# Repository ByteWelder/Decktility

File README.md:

# Decktility

Decktility is a handheld PC, inspired by [Yarh.io Micro 2](https://yarh.io/),
[uConsole](https://www.clockworkpi.com/uconsole) and various retro handheld PCs.

It is built with a Raspbery Pi CM4 and an 800x480 pixel IPS screen with capacitive touch.
A set of batteries is estimated to provide about 6 hours of power. (\*)

The original build log and learnings can be found on [ByteWelder.com](https://bytewelder.com/posts/2023/05/20/building-a-handheld-pc.html).

# Features & Specifications

- Compact design: `124.4 x 144.0 x 16.3 mm` (w x h x d). The battery lid portrudes by `10.2 mm`.
- Weighs approximately `375 g`. (depends on filament weight)
- Powered by a Raspberry Pi CM4 and a BTT Pad 5 (`800x480` resolution with capacitive touch)
- Replaceable batteries
- USB-C charging (~`10 W`)
- Power management

(\*) Using US18650VTC6 cells. Power draw was tested with an idle Discord tab in Chrome.

# Software

## Raspberry Pi

The Pi can be used with [Raspberry Pi OS](https://www.raspberrypi.com/software/) or any other Pi-compatible OS.

Check the to the [Pad 5 Manual](https://github.com/bigtreetech/Raspberry-Pad/tree/master/Pad5) for installing the OS and setting up some of the hardware.

## Arduino Nano / Power Manager

The [Power Manager](./powermanager) controls the power connection to the Pi and the keyboard. Power is enabled/disabled depending on the battery voltage.
The power manager measures battery and charging status, and can send it to the Pi. This enables battery status on the Pi desktop.
If something is not clear - or if you find an error, please open an issue on the GitHub project page.

Check out the [assembly guide](docs/assembling.md) for more details.

# Case

The latest printable parts are in the [printables](printables) folder.

The case is available as open hardware via OnShape:
- [v1.1](https://cad.onshape.com/documents/bcf3b5212bb2ba6496cfe6cf/v/382999b629ab56cddd2b7e21/e/5dfdd5987e1df112fcfa814b)
- [Main/WIP](https://cad.onshape.com/documents/bcf3b5212bb2ba6496cfe6cf/w/d70be68a60b4c80f684ba746/e/f2fb47dfa2dbdc91d7666ed1)

**Warning**: Don't print from the Main branch, because it will possibly have unfinished and/or untested changes.

# Building

Build this project at [your own risk](LICENSE.md).
The build guide might have flaws.
Working with batteries and electronics is not without risk.

- [Bill of materials](docs/bom.md)
- [Printing guide](docs/printing.md)
- [Assembling](docs/assembling.md)

# License

All hardware, software and other content in this project are licensed under `Attribution-ShareAlike 4.0 International (CC BY-SA 4.0)`.

See [LICENSE.md](LICENSE.md) for details. For a short overview and translations go to the [Creative Commons website](https://creativecommons.org/licenses/by-sa/4.0/legalcode).

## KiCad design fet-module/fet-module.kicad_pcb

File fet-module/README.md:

This is the KiCad project for the FET board, which acts as an electronic switch to turn on/off the hardware depending on available battery power.

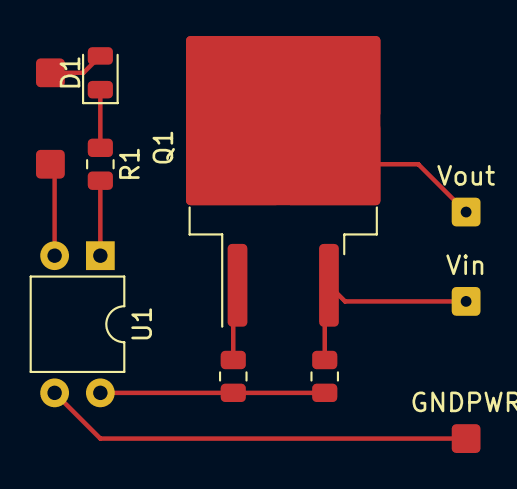
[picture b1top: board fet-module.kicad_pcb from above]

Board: 2 copper layers, 11 parts (0 on the bottom side), 9 nets.

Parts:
+5VD: SolderWire-0.1sqmm_1x01_D0.4mm_OD1mm
D1: LED; LED_0805_2012Metric
GNDD: SolderWire-0.1sqmm_1x01_D0.4mm_OD1mm
GNDPWR: SolderWire-0.1sqmm_1x01_D0.4mm_OD1mm
Q1: PMOS; TO-263-2
R1: 2.2k; R_0805_2012Metric
R2: 10k; R_0805_2012Metric
R3: 1M; R_0805_2012Metric
U1: PC817; DIP-4_W7.62mm
Vin: SolderWire-0.1sqmm_1x01_D0.4mm_OD1mm
Vout: SolderWire-0.1sqmm_1x01_D0.4mm_OD1mm

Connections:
+5VD: +5VD.1, D1.2 (A)
GNDD: GNDD.1, U1.2
GNDPWR: GNDPWR.1, U1.3
unnamed: D1.1 (K), R1.1
unnamed: Q1.1 (D), R2.2
unnamed: R1.2, U1.1
unnamed: R2.1, R3.2, U1.4
VD: Q1.2 (G), Vout.1
VDD: Q1.3 (S), R3.1, Vin.1

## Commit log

2023-05-02 added empty README.md
2023-05-02 added powermanager and powermanager-client
2023-05-02 fix link
2023-05-02 added link
2023-05-02 added OnShape
2023-05-03 added mockup image
2023-05-03 updated image
2023-05-03 added license
2023-05-03 added features
2023-05-03 added dimensions
2023-05-03 rephrased
2023-05-03 typo
2023-05-03 image update
2023-05-04 design update
2023-05-04 new graphic
2023-05-04 updated BOM
2023-05-04 fix left edge
2023-05-04 size limit test
2023-05-04 revert
2023-05-08 updated docs
2023-05-08 updated pics
2023-05-12 printing tips
2023-05-13 beta update
2023-05-13 center image
2023-05-13 updated project description
2023-05-13 added photo
2023-05-13 weight update
2023-05-13 battery life
2023-05-14 docs improved
2023-05-14 updated info about parts
2023-05-14 fixed bom pics links
2023-05-14 building notes
2023-05-14 move pics to docs folder
2023-05-14 added power manager info
2023-05-14 updated todo list
2023-05-14 updated todo list after fixes
2023-05-16 new fet docs
2023-05-16 new photo
2023-05-17 updated docs and gitignore
2023-05-18 ltc294x - first implementation
2023-05-18 updated README.md pics
2023-05-18 added reference docs and manual
2023-05-18 updated power manager and docs
2023-05-18 firmware fixes for battery capacity value
2023-05-18 added test script for i2c
2023-05-18 added wip notice
2023-05-19 fix for deleted header
2023-05-19 update for battery i2c fixes
2023-05-19 release v1.0
2023-05-19 removed beta notice
2023-05-19 simplifications
2023-05-19 docs updated
2023-05-19 added fan instructions
2023-05-19 improved wording on BMS
2023-05-19 fixed typo
2023-05-20 added wiring docs
2023-05-20 step typo fix
2023-05-20 improved disclaimer
2023-05-20 added github issue referral
2023-05-20 3d printing updates
2023-05-20 added pi soldering tips
2023-05-20 display buttons shim fix and docs
2023-05-20 link v1.1
2023-05-20 link to blog post
2023-05-21 new front page pic
2023-05-21 updated internals preview pic
2023-05-22 clarify battery life better
